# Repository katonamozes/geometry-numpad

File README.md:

# Geometry numpad
This macropad has a 12 buttons and will use the xiao rp2040 as a processor. I will use it to play geometry dash so that I don't destroy my laptops keyboard or my mouse. It also has a numpad because my laptop doesn't have one. 

## Features:
- Dual layer PCB
- 12 keys
    - 9 Numbers
    - 3 Mouse buttons

## Cad model
I designed the case in fusion 360 with 3d printing in mind. I designed it in 2 pieces: 1 for the pcb to sit on and 1 to keep the pcb in place.

## PCB
I made my PCB in kicad. I learned a lot making it as I had to use diodes which I haven't used before, I now know that they are directional and that I will need to watch out for how I put them in. 

Schematic

PCB

## Firmware overview
It uses QMK
I made it so that it has the 9 number keys and the other 3 are mouse keys but instead of having right middle and left click it has 2 left clicks and 1 right click. This is great for playing geometry dash as you can switch between 2 keys when you are playing instead of having to use just 1 key which sometimes isn't fast enough. 

Bom:
| Name | Purpose | Quantity | Total (USD) | Distributor | Link |
| ---- | ------- | -------- | ----------- | ----------- | ---- |
| Switches | For clicking | 20 | $3.01 | Aliexpress | https://nl.aliexpress.com/item/1005012157731141.html?spm=a2g0o.productlist.main.1.4d7bH1ByH1ByPs&algo_pvid=b3769f0c-f879-4f3b-b0dc-900350540a81&algo_exp_id=b3769f0c-f879-4f3b-b0dc-900350540a81-2&pdp_ext_f=%7B%22order%22%3A%22732%22%2C%22eval%22%3A%221%22%2C%22fromPage%22%3A%22search%22%7D&pdp_npi=6%40dis%21USD%213.87%211.73%21%21%2126.09%2111.63%21%402101f70717819438036221846eea14%2112000057665020941%21sea%21NL%217103435547%21X%211%210%21n_tag%3A-29919%3Bd%3Ae74134d9%3Bm03_new_user%3A-29895%3BpisId%3A5000000209383906&curPageLogUid=FWcbYS4cIixg&utparam-url=scene%3Asearch%7Cquery_from%3A%7Cx_object_id%3A1005012157731141%7C_p_origin_prod%3A |
| 1N4148 DIP diodes | For electricity management | 20 | $1.48 | Aliexpress | https://nl.aliexpress.com/item/32945649182.html?spm=a2g0o.productlist.main.2.3d15432akxQoEi&algo_pvid=62c69d8c-e35b-413f-92dd-fdf5121bb6d5&algo_exp_id=62c69d8c-e35b-413f-92dd-fdf5121bb6d5-1&pdp_ext_f=%7B%22order%22%3A%22231%22%2C%22eval%22%3A%221%22%2C%22fromPage%22%3A%22search%22%7D&pdp_npi=6%40dis%21USD%211.50%211.42%21%21%211.50%211.42%21%402101e2b017819439181502770e2a49%2112000057173949942%21sea%21NL%217103435547%21X%211%210%21n_tag%3A-29919%3Bd%3Ae74134d9%3Bm03_new_user%3A-29895%3BpisId%3A5000000209393528&curPageLogUid=sU3M2rU6byXa&utparam-url=scene%3Asearch%7Cquery_from%3A%7Cx_object_id%3A32945649182%7C_p_origin_prod%3A |
| Xiao Rp2040 | For processing | 1 | $15.61 | Aliexpress | https://nl.aliexpress.com/item/1005007427287029.html?spm=a2g0o.productlist.main.3.75115e6drW59z1&algo_pvid=50d09283-316f-4cb8-9c4b-bbcacb378db4&algo_exp_id=50d09283-316f-4cb8-9c4b-bbcacb378db4-2&pdp_ext_f=%7B%22order%22%3A%2283%22%2C%22eval%22%3A%221%22%2C%22fromPage%22%3A%22search%22%7D&pdp_npi=6%40dis%21USD%2116.08%2115.44%21%21%2116.08%2115.44%21%402101e2b017819436264412765e2aa6%2112000040716641980%21sea%21NL%217103435547%21X%211%210%21n_tag%3A-29919%3Bd%3Ae74134d9%3Bm03_new_user%3A-29895%3BpisId%3A5000000209378863&curPageLogUid=k1qg5lux2qlA&utparam-url=scene%3Asearch%7Cquery_from%3A%7Cx_object_id%3A1005007427287029%7C_p_origin_prod%3A |

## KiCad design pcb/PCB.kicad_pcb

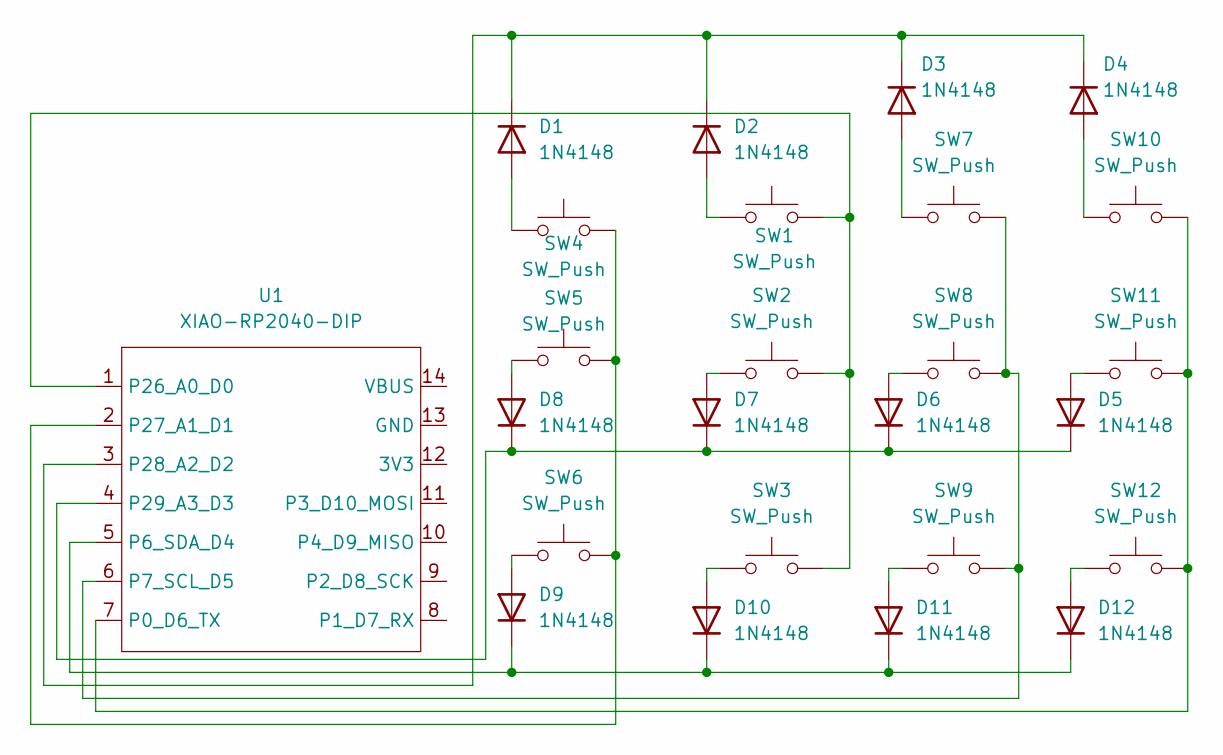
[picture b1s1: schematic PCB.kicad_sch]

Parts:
D1, D2, D3, D4, D5, D6, D7, D8, D9, D10, D11, D12: 1N4148; C_Disc_D16.0mm_W5.0mm_P10.00mm
SW1, SW2, SW3, SW4, SW5, SW6, SW7, SW8, SW9, SW10, SW11, SW12: SW_Push; MX-Solderable-1U
U1: XIAO-RP2040-DIP

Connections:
unnamed: D1.2 (A), SW4.1
unnamed: D1.1 (K), D2.1 (K), D3.1 (K), D4.1 (K), U1.3 (P28_A2_D2)
unnamed: D2.2 (A), SW1.1
unnamed: D3.2 (A), SW7.1
unnamed: D4.2 (A), SW10.1
unnamed: D5.2 (A), SW11.1
unnamed: D5.1 (K), D6.1 (K), D7.1 (K), D8.1 (K), U1.4 (P29_A3_D3)
unnamed: D6.2 (A), SW8.1
unnamed: D7.2 (A), SW2.1
unnamed: D8.2 (A), SW5.1
unnamed: D9.2 (A), SW6.1
unnamed: D10.2 (A), SW3.1
unnamed: D9.1 (K), D10.1 (K), D11.1 (K), D12.1 (K), U1.5 (P6_SDA_D4)
unnamed: D11.2 (A), SW9.1
unnamed: D12.2 (A), SW12.1
unnamed: SW10.2, SW11.2, SW12.2, U1.7 (P0_D6_TX)
unnamed: SW7.2, SW8.2, SW9.2, U1.6 (P7_SCL_D5)
unnamed: SW1.2, SW2.2, SW3.2, U1.1 (P26_A0_D0)
unnamed: SW4.2, SW5.2, SW6.2, U1.2 (P27_A1_D1)

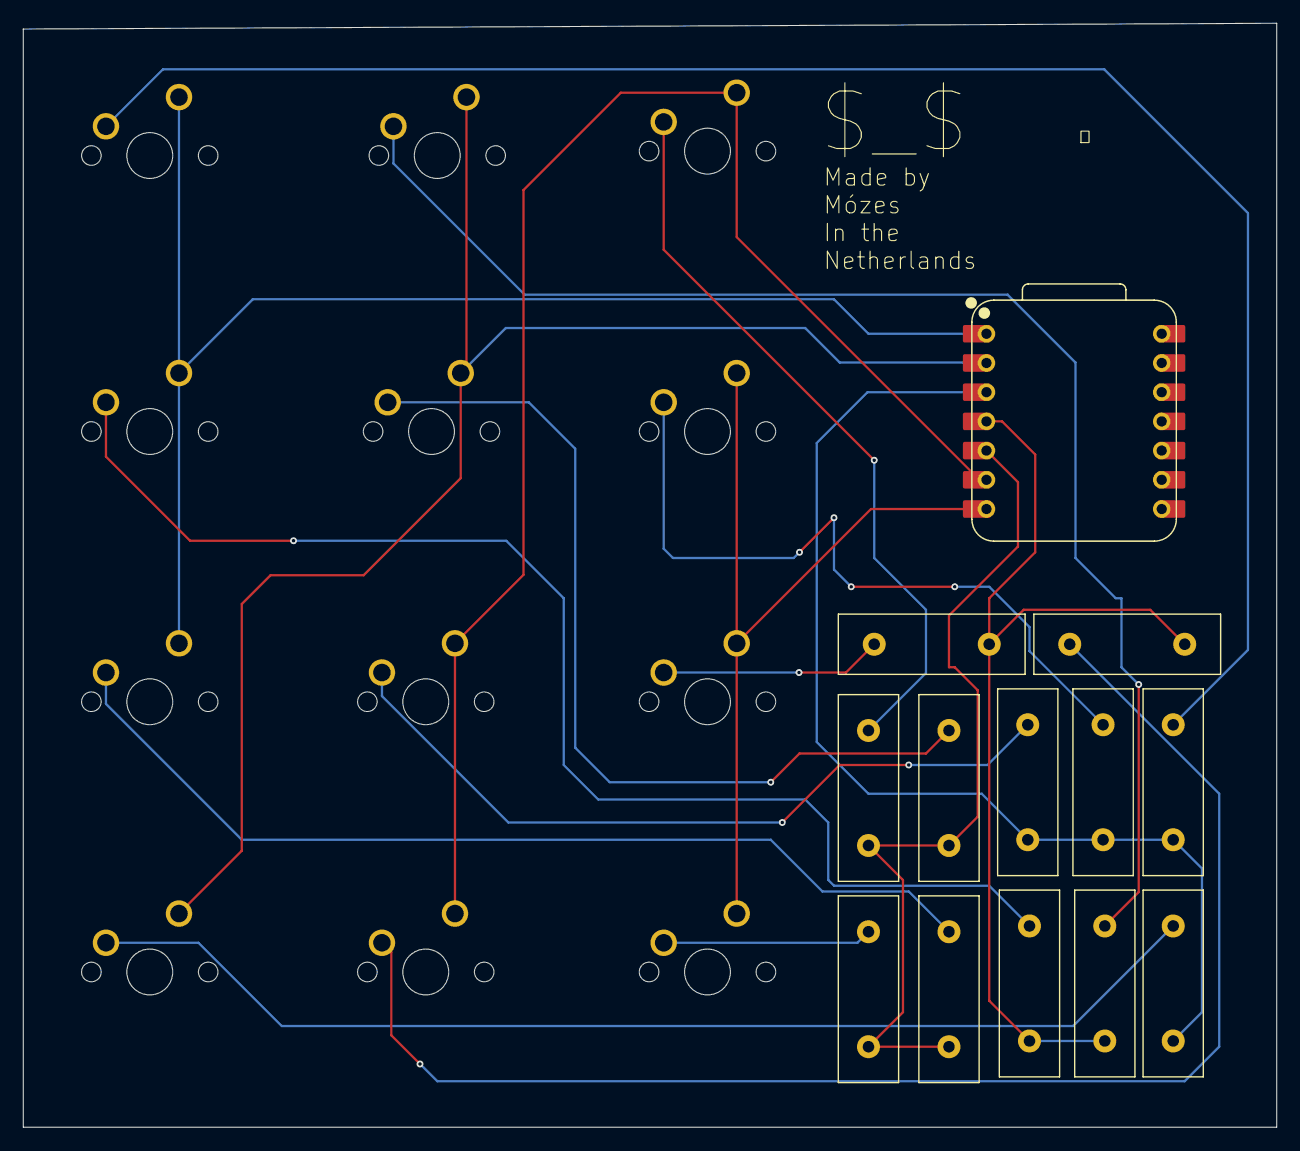
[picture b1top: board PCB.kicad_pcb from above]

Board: 2 copper layers, 109.0 x 96.0 mm, 25 parts (0 on the bottom side), 19 nets.

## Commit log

2026-06-20 Add BOM section to README
    Added a bill of materials (BOM) section with details on components used for the macropad.
2026-06-21 Add images to README for macropad project
    Added images to the README for better visualization.
2026-06-26 Enhance README with features and design details
    Added detailed sections about features, CAD model, PCB design, and firmware overview.
